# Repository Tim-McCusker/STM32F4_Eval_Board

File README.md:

# STM32F4 Evaluation Board

## My version of Phil's Labs' STM32F4 Evaluation Board and my first PCB design attempt. ##  

Key enhancements in my version of the project include: 
- Added ST Microelectronics i-NEMO I2C Inerital Measurement Unit 
- Added on-board temperature sensor 
- Alternate DC/DC Converter selection and power electronics circuitry 
- R2D2  

Please also check out the original design and tutorial series: 
    
GitHub: https://github.com/pms67/STM32F4-Reference-PCB

YouTube: https://www.youtube.com/channel/UCVryWqJ4cSlbTSETBHpBUWw

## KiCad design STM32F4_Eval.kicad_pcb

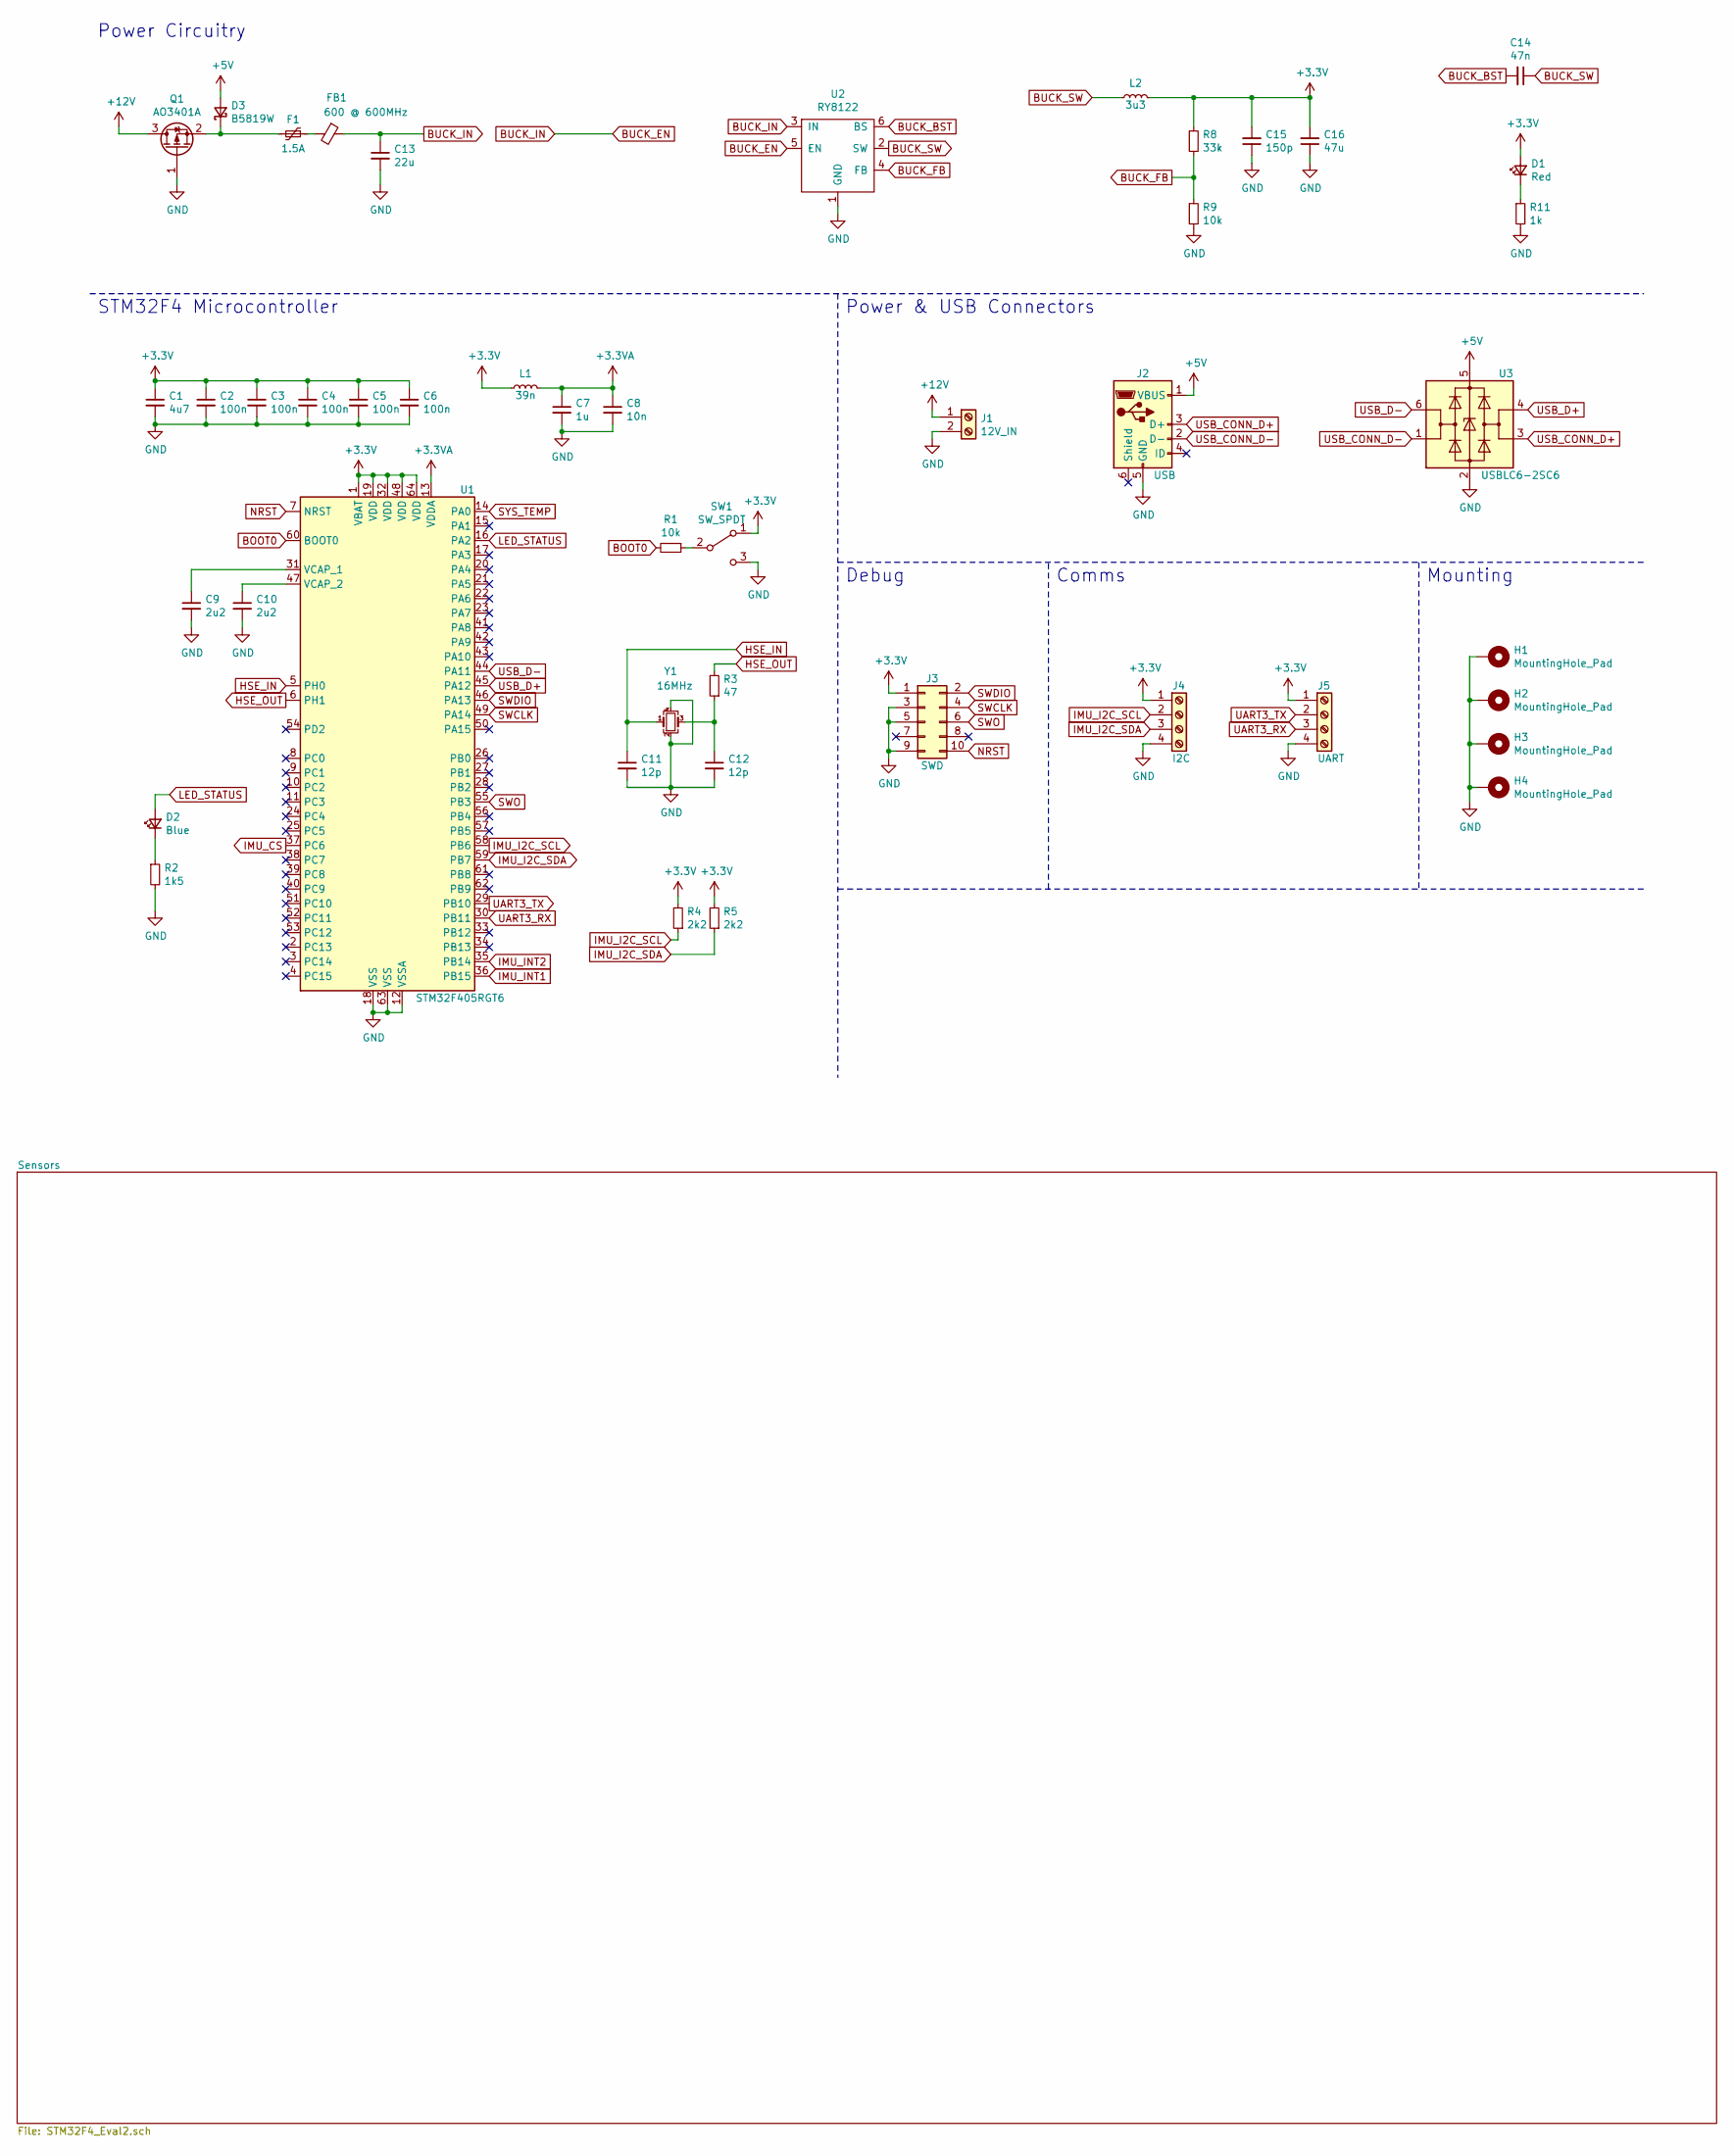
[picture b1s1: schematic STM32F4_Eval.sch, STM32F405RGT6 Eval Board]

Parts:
C1: 4u7; C_0603_1608Metric; LCSC Part # C19666
C2, C3, C4, C5, C6: 100n; C_0402_1005Metric; LCSC Part # C1525
C7: 1u; C_0402_1005Metric; LCSC Part # C52923
C8: 10n; C_0402_1005Metric; LCSC Part # C15195
C9, C10: 2u2; C_0603_1608Metric; LCSC Part # C23630
C11, C12: 12p; C_0402_1005Metric; LCSC Part # C1547
C13: 22u; C_1206_3216Metric; LCSC Part # C50254
C14: 47n; C_0402_1005Metric; LCSC Part # C26403
C15: 150p; C_0805_2012Metric; LCSC Part # C1716
C16: 47u; C_1206_3216Metric; LCSC Part # C96123
D1: Red; LED_0603_1608Metric; LCSC Part # C2286
D2: Blue; LED_0603_1608Metric; LCSC Part # C72041
D3: B5819W; D_SOD-123; LCSC Part # C8598
F1: 1.5A; Fuse_1206_3216Metric; LCSC Part # C369159
FB1: 600 @ 600MHz; L_0805_2012Metric; LCSC Part # C1017
H1, H2, H3, H4: MountingHole_Pad; MountingHole_4.3mm_M4_Pad_Via
J1: 12V_IN; TerminalBlock_Phoenix_PT-1,5-2-3.5-H_1x02_P3.50mm_Horizontal
J2: USB; USB_Micro-B_Molex-105017-0001
J3: SWD; PinHeader_2x05_P1.27mm_Vertical_SMD
J4: I2C; TerminalBlock_Phoenix_MKDS-1,5-4-5.08_1x04_P5.08mm_Horizont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
J5: UART; TerminalBlock_Phoenix_MKDS-1,5-4-5.08_1x04_P5.08mm_Horizont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
L1: 39n; L_0402_1005Metric; LCSC Part # C26443
L2: 3u3; L_Sunlord_MWSA0518_5.4x5.2mm; LCSC Part # C408410
Q1: AO3401A; SOT-23; LCSC Part # C15127
R1: 10k; R_0402_1005Metric; LCSC Part # C25744
R2: 1k5; R_0603_1608Metric; LCSC Part # C22843
R3: 47; R_0402_1005Metric; LCSC Part # C25792
R4, R5: 2k2; R_0402_1005Metric; LCSC Part # C25879
R8: 33k; R_0603_1608Metric; LCSC Part # C4216
R9: 10k; R_0603_1608Metric; LCSC Part # C25804
R11: 1k; R_0603_1608Metric; LCSC Part # C21190
SW1: SW_SPDT; SW_SPDT_PCM12
U1: STM32F405RGT6; LQFP-64_10x10mm_P0.5mm; LCSC Part # C15742
U2: RY8122; SOT-23-6; LCSC Part # C370758
U3: USBLC6-2SC6; SOT-23-6; LCSC Part # C7519
Y1: 16MHz; Crystal_SMD_3225-4Pin_3.2x2.5mm; LCSC Part # C13738

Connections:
+3.3VA: C7.1, C8.1, L1.2, U1.13 (VDDA)
+3V3: C1.1, C2.1, C3.1, C4.1, C5.1, C6.1, C15.2, C16.2, D1.2 (A), J3.1, J4.1, J5.1, L1.1, L2.2, R4.2, R5.2, R8.1, SW1.1 (A), U1.1 (VBAT), U1.19 (VDD), U1.32 (VDD), U1.48 (VDD), U1.64 (VDD); also elsewhere on the board
+5V: D3.2 (A), J2.1 (VBUS), U3.5 (VBUS)
+12V: J1.1, Q1.3 (D)
BOOT0: R1.2, U1.60 (BOOT0)
BUCK_BST: C14.2, U2.6 (BS)
BUCK_EN: C13.1, FB1.1, U2.3 (IN), U2.5 (EN)
BUCK_FB: R8.2, R9.1, U2.4 (FB)
BUCK_SW: C14.1, L2.1, U2.2 (SW)
GND: C1.2, C2.2, C3.2, C4.2, C5.2, C6.2, C7.2, C8.2, C9.2, C10.2, C11.2, C12.2, C13.2, C15.1, C16.1, H1.1, H2.1, H3.1, H4.1, J1.2, J2.5 (GND), J3.3, J3.5, J3.9, J4.4, J5.4, Q1.1 (G), R2.2, R9.2, R11.2, SW1.3 (C), U1.12 (VSSA), U1.18 (VSS), U1.63 (VSS), U2.1 (GND), U3.2 (GND), Y1.2, Y1.4; also elsewhere on the board
HSE_IN: C11.1, U1.5 (PH0), Y1.1
HSE_OUT: R3.2, U1.6 (PH1)
IMU_CS: U1.37 (PC6); also elsewhere on the board
IMU_I2C_SCL: J4.2, R4.1, U1.58 (PB6); also elsewhere on the board
IMU_I2C_SDA: J4.3, R5.1, U1.59 (PB7); also elsewhere on the board
IMU_INT1: U1.36 (PB15); also elsewhere on the board
IMU_INT2: U1.35 (PB14); also elsewhere on the board
LED_STATUS: D2.2 (A), U1.16 (PA2)
NRST: J3.10, U1.7 (NRST)
unnamed: C9.1, U1.31 (VCAP_1)
unnamed: C10.1, U1.47 (VCAP_2)
unnamed: C12.1, R3.1, Y1.3
unnamed: D1.1 (K), R11.1
unnamed: D2.1 (K), R2.1
unnamed: D3.1 (K), F1.2, Q1.2 (S)
unnamed: F1.1, FB1.2
unnamed: R1.1, SW1.2 (B)
SWCLK: J3.4, U1.49 (PA14)
SWDIO: J3.2, U1.46 (PA13)
SWO: J3.6, U1.55 (PB3)
SYS_TEMP: U1.14 (PA0); also elsewhere on the board
UART3_RX: J5.3, U1.30 (PB11)
UART3_TX: J5.2, U1.29 (PB10)
USB_CONN_D+: J2.3 (D+), U3.3 (I/O2)
USB_CONN_D-: J2.2 (D-), U3.1 (I/O1)
USB_D+: U1.45 (PA12), U3.4 (I/O2)
USB_D-: U1.44 (PA11), U3.6 (I/O1)

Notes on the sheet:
Power & USB Connectors
Debug
Comms
STM32F4 Microcontroller
Power Circuitry
Mounting

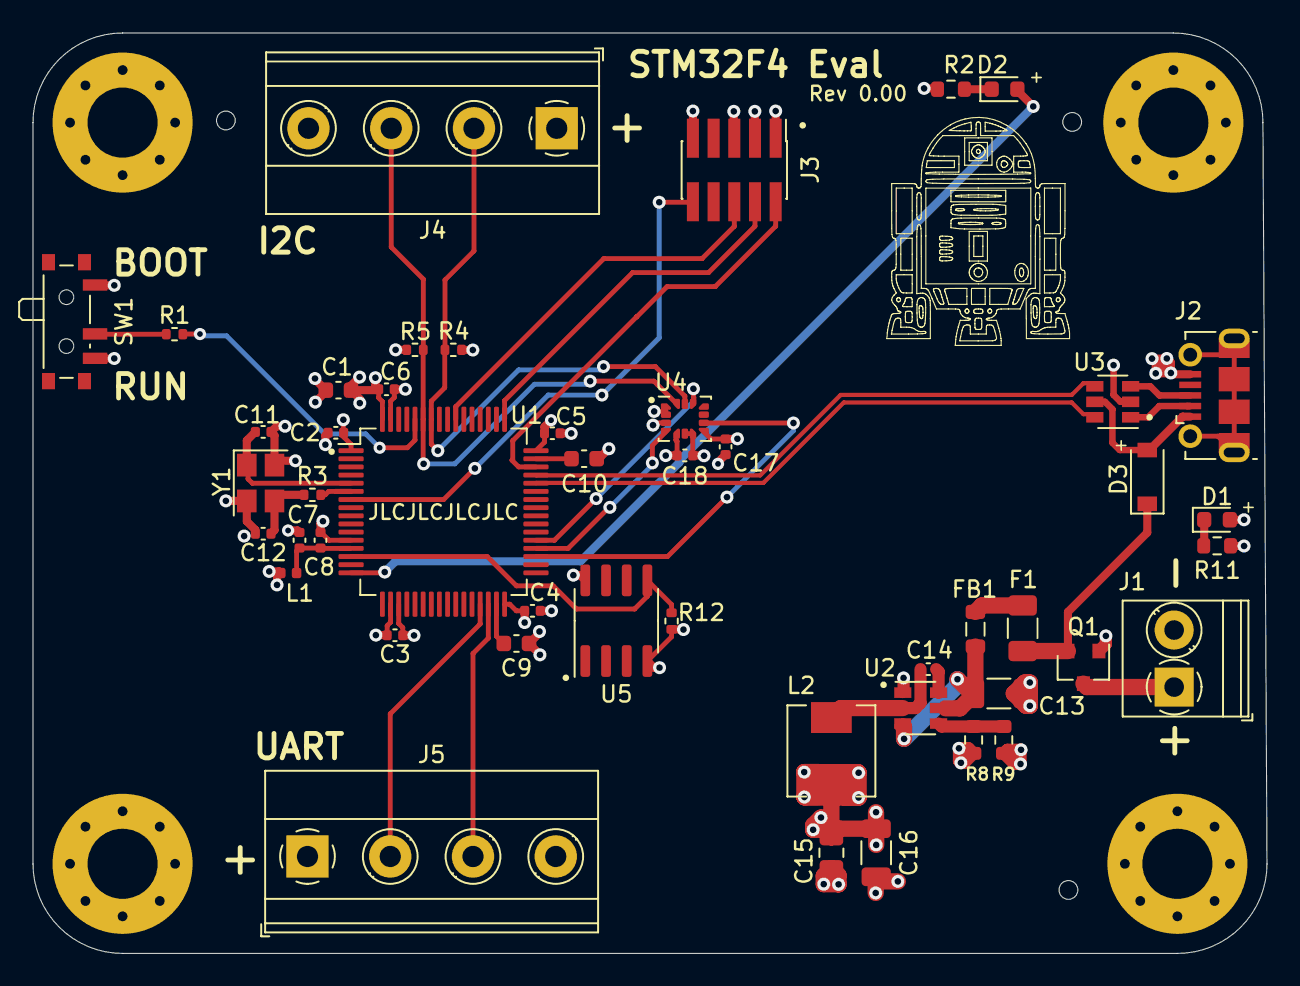
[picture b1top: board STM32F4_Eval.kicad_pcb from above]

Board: 4 copper layers, 75.8 x 56.5 mm, 51 parts (0 on the bottom side), 37 nets.

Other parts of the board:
C17, C18: 100n; C_0402_1005Metric
R12: 10k; R_0402_1005Metric
U4: LSM6DS3; LGA-14_3x2.5mm_P0.5mm_LayoutBorder3x4y
U5: LM335ADT; SOIC-8_3.9x4.9mm_P1.27mm

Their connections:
+3V3: C17.2, C18.1, U4.5, U4.8, U5.8; also elsewhere on the board
GND: C17.1, C18.2, R12.2, U4.1, U4.2, U4.3, U4.6, U4.7, U5.4; also elsewhere on the board
IMU_CS: U4.12; also elsewhere on the board
IMU_I2C_SCL: U4.13; also elsewhere on the board
IMU_I2C_SDA: U4.14; also elsewhere on the board
IMU_INT1: U4.4; also elsewhere on the board
IMU_INT2: U4.9; also elsewhere on the board
SYS_TEMP: R12.1, U5.5; also elsewhere on the board

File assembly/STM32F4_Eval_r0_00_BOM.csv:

Comment,Designator,Footprint,LCSC Part #
"4u7 Unpolarized capacitor, small symbol",C1,C_0603_1608Metric,"C19666"
"100n Unpolarized capacitor, small symbol","C2,C3,C4,C5,C6,C17,C18",C_0402_1005Metric,"C1525"
"1u Unpolarized capacitor, small symbol",C7,C_0402_1005Metric,"C52923"
"10n Unpolarized capacitor, small symbol",C8,C_0402_1005Metric,"C15195"
"2u2 Unpolarized capacitor, small symbol","C9,C10",C_0603_1608Metric,"C23630"
"12p Unpolarized capacitor, small symbol","C11,C12",C_0402_1005Metric,"C1547"
"22u Unpolarized capacitor, small symbol",C13,C_1206_3216Metric,"C50254"
"47n Unpolarized capacitor, small symbol",C14,C_0402_1005Metric,"C26403"
"150p Unpolarized capacitor, small symbol",C15,C_0805_2012Metric,"C1716"
"47u Unpolarized capacitor, small symbol",C16,C_1206_3216Metric,"C96123"
"Red Light emitting diode, small symbol",D1,LED_0603_1608Metric,"C2286"
"Blue Light emitting diode, small symbol",D2,LED_0603_1608Metric,"C72041"
"B5819W Schottky diode, small symbol",D3,D_SOD-123,"C8598"
"1.5A Resettable fuse, polymeric positive temperature coefficient, small symbol",F1,Fuse_1206_3216Metric,"C369159"
"600 @ 600MHz Ferrite bead, small symbol",FB1,L_0805_2012Metric,"C1017"
MountingHole_Pad Mounting Hole with connection,"H1,H2,H3,H4",MountingHole_4.3mm_M4_Pad_Via,""
"12V_IN Generic screw terminal, single row, 01x02, script generated (kicad-library-utils/schlib/autogen/connector/)",J1,"TerminalBlock_Phoenix_PT-1,5-2-3.5-H_1x02_P3.50mm_Horizontal",""
USB USB Micro Type B connector,J2,USB_Micro-B_Molex-105017-0001,""
"SWD Generic connector, double row, 02x05, odd/even pin numbering scheme (row 1 odd numbers, row 2 even numbers), script generated (kicad-library-utils/schlib/autogen/connector/)",J3,PinHeader_2x05_P1.27mm_Vertical_SMD,""
"I2C Generic screw terminal, single row, 01x04, script generated (kicad-library-utils/schlib/autogen/connector/)",J4,"TerminalBlock_Phoenix_MKDS-1,5-4-5.08_1x04_P5.08mm_Horizontal",""
"UART Generic screw terminal, single row, 01x04, script generated (kicad-library-utils/schlib/autogen/connector/)",J5,"TerminalBlock_Phoenix_MKDS-1,5-4-5.08_1x04_P5.08mm_Horizontal",""
"39n Inductor, small symbol",L1,L_0402_1005Metric,"C26443"
"3u3 Inductor, small symbol",L2,L_Sunlord_MWSA0518_5.4x5.2mm,"C408410"
"AO3401A -4.0A Id, -30V Vds, P-Channel MOSFET, SOT-23",Q1,SOT-23,"C15127"
"10k Resistor, small symbol","R1,R12",R_0402_1005Metric,"C25744"
"1k5 Resistor, small symbol",R2,R_0603_1608Metric,"C22843"
"47 Resistor, small symbol",R3,R_0402_1005Metric,"C25792"
"2k2 Resistor, small symbol","R4,R5",R_0402_1005Metric,"C25879"
"33k Resistor, small symbol",R8,R_0603_1608Metric,"C4216"
"10k Resistor, small symbol",R9,R_0603_1608Metric,"C25804"
"1k Resistor, small symbol",R11,R_0603_1608Metric,"C21190"
"SW_SPDT Switch, single pole double throw",SW1,SW_SPDT_PCM12,""
"STM32F405RGT6 ARM Cortex-M4 MCU, 1024KB flash, 128KB RAM, 168MHz, 1.8-3.6V, 51 GPIO, LQFP-64",U1,LQFP-64_10x10mm_P0.5mm,"C15742"
RY8122 ,U2,SOT-23-6,"C370758"
"USBLC6-2SC6 Very low capacitance ESD protection diode, 2 data-line, SOT-23-6",U3,SOT-23-6,"C7519"
"LSM6DS3 I2C/SPI, iNEMO inertial module: always-on 3D accelerometer and 3D gyroscope",U4,LGA-14_3x2.5mm_P0.5mm_LayoutBorder3x4y,"C95231"
LM335ADT ,U5,SOIC-8_3.9x4.9mm_P1.27mm,"C361027"
"16MHz Four pin crystal, GND on pins 2 and 4, small symbol",Y1,Crystal_SMD_3225-4Pin_3.2x2.5mm,"C13738"
